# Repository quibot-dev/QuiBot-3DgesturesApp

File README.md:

# Qui-Bot H₂O
Documentació oficial i codi del Projecte QuiBot (UPC).

🌐 **Lloc web del projecte:** [https://quibot.upc.edu]

Robot humanoide educatiu que introdueix la programació seqüencial i la química
a infants de primària. Es mou per un tauler de joc amb línies negres, seguint
seqüències d'ordres, i manipula líquids de colors amb dues xeringues.

Admet tres vies de control:

- **Blocs de colors.** S'hi introdueixen cubs de fusta i el robot en llegeix el
  color i executa l'acció corresponent. És la via original del projecte.
- **Gestos.** Un sensor davant la cara reconeix sis ordres de moviment, amb
  confirmació abans d'executar-les.
- **Control remot per Wi-Fi.** El robot serveix una pàgina web que s'obre des
  del navegador de qualsevol telèfon o ordinador de la mateixa xarxa, sense
  instal·lar res.

## Contingut del repositori

| Directori | Contingut |
|---|---|
| `3D/` | Peces en STL, fitxers de disseny, model del conjunt en FreeCAD, captures amb l'orientació d'impressió i els paràmetres de cada perfil |
| `PCB/` | Projecte KiCad, fitxers de fabricació en Gerber, esquema elèctric i vista 3D |
| `src/` | Programa de control, servidor web i programes de verificació |
| `doc/` | Llista de material i memòria del treball |
| `User_manual/` | Guia d'ús del robot per a tallers i vídeo de demostració |

La **guia de muntatge**, de trenta-set passos, és l'annex A de la memòria.

## Maquinari

El control corre sobre una **Raspberry Pi Zero W** muntada sobre una placa
dissenyada per al projecte. Els motors pas a pas es governen amb controladors
A4988 i els polsos es generen per programari amb `pigpio`.

Els sensors són el TCS34725 per al color dels blocs, el PAJ7620U2 per als
gestos, el VL53L0X per a la distància als recipients i dos TCRT5000 per al
seguiment de línia, llegits a través d'un convertidor ADS1115. Els ulls són
dues matrius de LED WS2811.

## Posada en marxa

Cal Raspberry Pi OS Lite de 32 bits. El procediment complet és a l'annex D de
la memòria; en resum:

**1. Busos i pins.** Afegiu a `/boot/firmware/config.txt`:

```
dtparam=i2c_arm=on
dtoverlay=i2c-gpio,bus=3,i2c_gpio_sda=0,i2c_gpio_scl=1
gpio=4,5,6=op,dh
```

La tercera línia imposa nivell alt als pins d'habilitació dels controladors des
de l'arrencada i evita que els motors quedin energitzats i brunzint.

**2. Mòdul d'accés als busos:**

```bash
sudo modprobe i2c-dev
echo i2c-dev | sudo tee -a /etc/modules
```

Reinicieu. `ls /dev/i2c-*` ha de mostrar els dos busos.

**3. Entorn de Python:**

```bash
python3 -m venv ~/.venv
~/.venv/bin/pip install pigpio smbus2 flask rpi_ws281x \
    adafruit-circuitpython-ads1x15 \
    adafruit-circuitpython-tcs34725 \
    adafruit-circuitpython-vl53l0x \
    adafruit-extended-bus
```

**4. Dimoni de control dels pins:**

```bash
sudo systemctl enable --now pigpiod
```

**5. Execució:**

```bash
~/.venv/bin/python3 quibot.py
```

El programa escriu a la sortida l'adreça del control remot, que escolta al
port 8000. Per arrencar-lo automàticament amb la màquina, l'annex D descriu el
servei de systemd corresponent.

Els programes de `src/tests/` permeten comprovar els motors i cada sensor per
separat, cosa que convé fer amb la placa encara accessible.

## Procedència i llicències

L'estructura mecànica i el disseny original del robot provenen del projecte
[Qui-Bot H₂O de La Codornella](https://github.com/lacodornella/QuiBot), d'on
surten també les captures d'orientació d'impressió que es reprodueixen aquí.
Dues peces s'han redissenyat i la placa de control és obra de l'equip del
projecte. El control per gestos, el control remot i la documentació són feina
d'aquest treball.

| Element | Llicència |
|---|---|
| Maquinari: peces 3D, PCB i Gerbers | CERN-OHL-S v2 |
| Programari: codi de control | GPL v3 |
| Documentació: guia de muntatge, BOM i manual | CC BY-SA 4.0 |

Totes tres són recíproques: permeten usar, modificar i redistribuir el
material amb la condició que les obres derivades es publiquin en les mateixes
condicions.

> 📢 **Aviseu-nos si feu servir o adapteu aquest material!**  
> Si teniu pensat replicar el projecte, utilitzar aquest material en la vostra recerca o desenvolupar una versió derivada, us agrairem molt que ens ho feu saber enviant un correu a [quibot@upc.edu](mailto:quibot@upc.edu) o obrint una *Issue* en aquest repositori. Això ens ajuda a fer el seguiment de l'impacte del projecte.

---

## 👥 Autors, Equip i Agraïments

* **Investigadors Principals:** Marta Tarrés i Toni Dorado — Grup de Recerca RISS, Universitat Politècnica de Catalunya (UPC).
* **Desenvolupament i Integració (TFG/TFM):** Pau Anguera Comas 
* **Finançament:** Projecte finançat pel Departament d'Igualtat i Feminismes de la Generalitat de Catalunya (`IFE038/24/000087`).

* ## ⚠️ Avís Legal, Seguretat i Suport

* **Exempció de responsabilitat:** Aquest repositori i tots els seus materials es proporcionen "tal com són" (*AS IS*), amb fins exclusivament docents i de recerca. Els autors i la Universitat Politècnica de Catalunya (UPC) no assumeixen cap responsabilitat per danys directes, indirectes o derivats de la fabricació, muntatge, manipulació o ús dels dissenys, circuits o codis d'aquest projecte.
* **Seguretat mecatrònica:** El dispositiu conté components elèctrics i elements mecànics en moviment. Cal prendre les precaucions de seguretat adients durant la seva manipulació i alimentació elèctrica.
* **Atenció i suport tècnic:** Aquest projecte es manté exclusivament en el marc de les activitats de recerca del grup RISS. L'equip investigador no assumeix cap compromís d'oferir assistència tècnica, suport personalitzat o resolució de peticions a tercers usuaris.

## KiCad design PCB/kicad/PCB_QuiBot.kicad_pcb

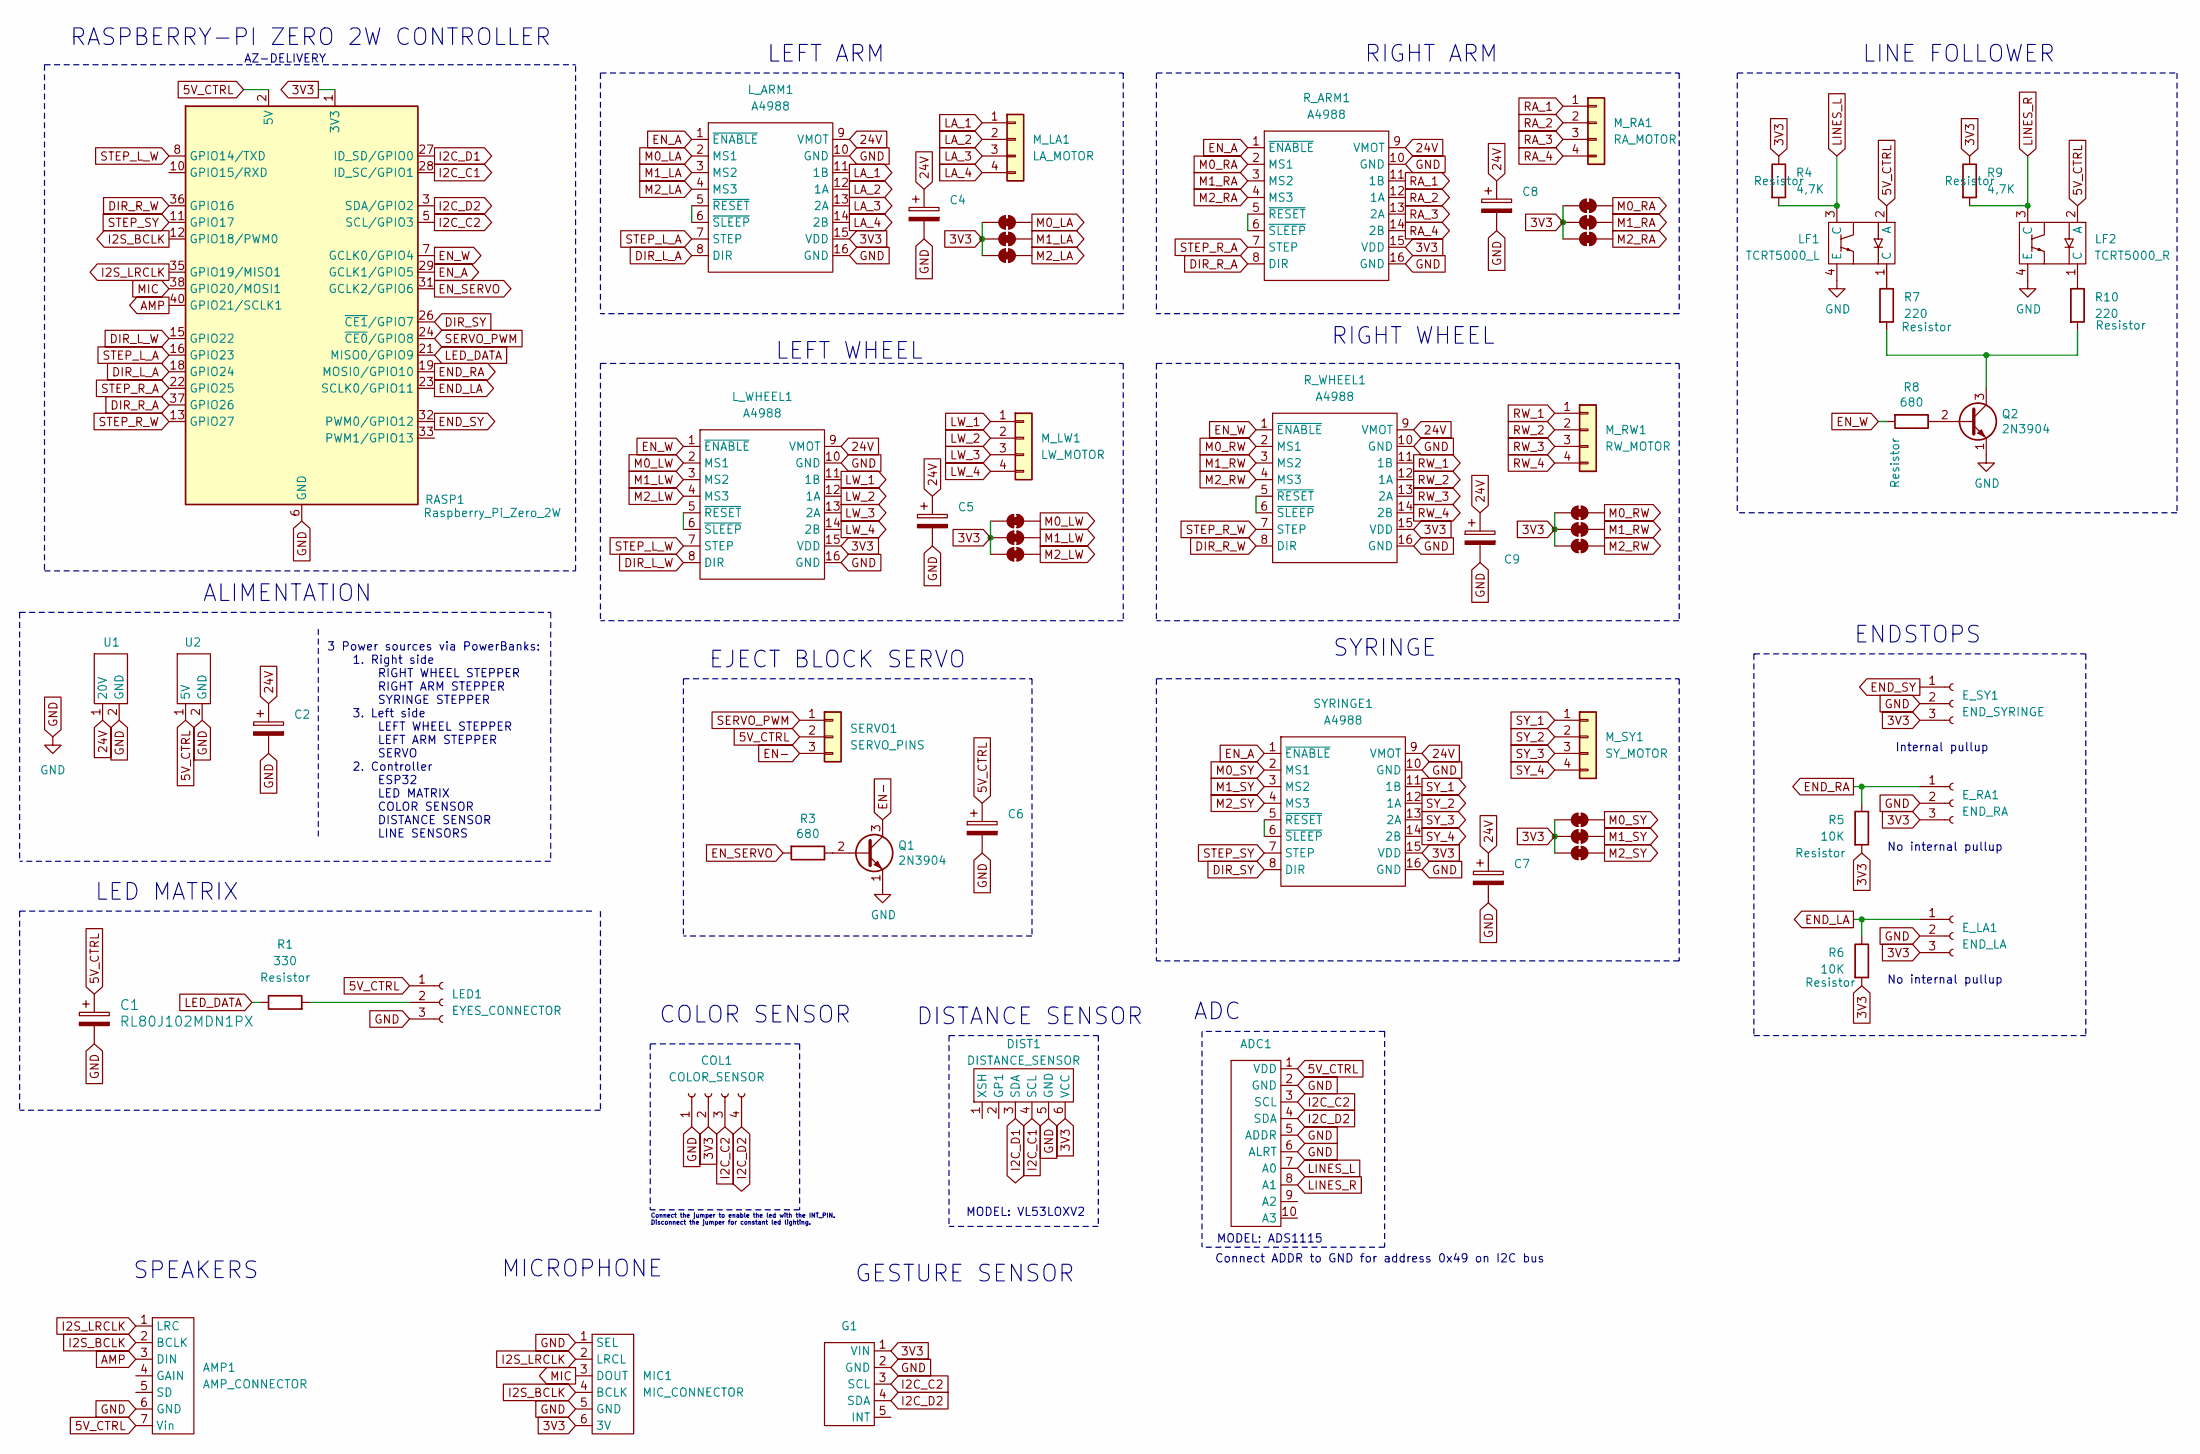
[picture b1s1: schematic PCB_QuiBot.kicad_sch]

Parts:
ADC1: PinHeader_1x10_P2.54mm_Vertical
AMP1: AMP_CONNECTOR; PinHeader_1x07_P2.54mm_Vertical
C1: RL80J102MDN1PX; CAP_RE5_8X8_NCH
C2: C_Polarized; CP_Radial_D10.0mm_P5.00mm
C4, C5, C6, C7, C8, C9: C_Polarized; CP_Radial_D6.3mm_P2.50mm
COL1: COLOR_SENSOR; PinHeader_1x04_P2.54mm_Vertical
DIST1: DISTANCE_SENSOR; PinHeader_1x06_P2.54mm_Vertical
E_LA1: END_LA; PinHeader_1x03_P2.54mm_Vertical
E_RA1: END_RA; PinHeader_1x03_P2.54mm_Vertical
E_SY1: END_SYRINGE; PinHeader_1x03_P2.54mm_Vertical
G1: PinHeader_1x05_P2.54mm_Vertical
LA0, LA1, LA2: SolderJumper_2_Bridged; SolderJumper-2_P1.3mm_Open_RoundedPad1.0x1.5mm
LED1: EYES_CONNECTOR; PinHeader_1x03_P2.54mm_Vertical
LF1: TCRT5000_L; TCRT5000_Line_follower
LF2: TCRT5000_R; TCRT5000_Line_follower
LW0, LW1, LW2: SolderJumper_2_Bridged; SolderJumper-2_P1.3mm_Open_RoundedPad1.0x1.5mm
L_ARM1: A4988; A4988_stepper_driver
L_WHEEL1: A4988; A4988_stepper_driver
MIC1: MIC_CONNECTOR; PinHeader_1x06_P2.54mm_Vertical
M_LA1: LA_MOTOR; PinHeader_1x04_P2.54mm_Vertical
M_LW1: LW_MOTOR; PinHeader_1x04_P2.54mm_Vertical
M_RA1: RA_MOTOR; PinHeader_1x04_P2.54mm_Vertical
M_RW1: RW_MOTOR; PinHeader_1x04_P2.54mm_Vertical
M_SY1: SY_MOTOR; PinHeader_1x04_P2.54mm_Vertical
Q1, Q2: 2N3904; TO-92_Inline
R1: 330; R_Axial_DIN0207_L6.3mm_D2.5mm_P10.16mm_Horizontal
R3, R8: 680; R_Axial_DIN0207_L6.3mm_D2.5mm_P10.16mm_Horizontal
R4, R9: 4,7K; R_Axial_DIN0207_L6.3mm_D2.5mm_P10.16mm_Horizontal
R5, R6: 10K; R_Axial_DIN0207_L6.3mm_D2.5mm_P10.16mm_Horizontal
R7, R10: 220; R_Axial_DIN0207_L6.3mm_D2.5mm_P10.16mm_Horizontal
RA0, RA1, RA2: SolderJumper_2_Bridged; SolderJumper-2_P1.3mm_Open_RoundedPad1.0x1.5mm
RASP1: Raspberry_Pi_Zero_2W; PinHeader_2x20_P2.54mm_Vertical
RW0, RW1, RW2: SolderJumper_2_Bridged; SolderJumper-2_P1.3mm_Open_RoundedPad1.0x1.5mm
R_ARM1: A4988; A4988_stepper_driver
R_WHEEL1: A4988; A4988_stepper_driver
SERVO1: SERVO_PINS; PinHeader_1x03_P2.54mm_Vertical
SY0, SY1, SY2: SolderJumper_2_Bridged; SolderJumper-2_P1.3mm_Open_RoundedPad1.0x1.5mm
SYRINGE1: A4988; A4988_stepper_driver
U1, U2: PowerConnector

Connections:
3V3: COL1.2, DIST1.6 (VCC), E_LA1.3, E_RA1.3, E_SY1.3, G1.1 (VIN), LA0.1 (A), LA1.1 (A), LA2.1 (A), LW0.1 (A), LW1.1 (A), LW2.1 (A), L_ARM1.15 (VDD), L_WHEEL1.15 (VDD), MIC1.6 (3V), R4.1, R5.2, R6.2, R9.1, RA0.1 (A), RA1.1 (A), RA2.1 (A), RASP1.1 (3V3), RASP1.17 (3V3), RW0.1 (A), RW1.1 (A), RW2.1 (A), R_ARM1.15 (VDD), R_WHEEL1.15 (VDD), SY0.1 (A), SY1.1 (A), SY2.1 (A), SYRINGE1.15 (VDD)
24V: C2.1, C4.1, C5.1, C7.1, C8.1, C9.1, L_ARM1.9 (VMOT), L_WHEEL1.9 (VMOT), R_ARM1.9 (VMOT), R_WHEEL1.9 (VMOT), SYRINGE1.9 (VMOT), U1.1 (20V)
AMP: AMP1.3 (DIN), RASP1.40 (GPIO21/SCLK1)
DIR_L_A: L_ARM1.8 (DIR), RASP1.18 (GPIO24)
DIR_L_W: L_WHEEL1.8 (DIR), RASP1.15 (GPIO22)
DIR_R_A: RASP1.37 (GPIO26), R_ARM1.8 (DIR)
DIR_R_W: RASP1.36 (GPIO16), R_WHEEL1.8 (DIR)
DIR_SY: RASP1.26 (~CE1/GPIO7), SYRINGE1.8 (DIR)
EN-: Q1.3 (C), SERVO1.3
END_LA: E_LA1.1, R6.1, RASP1.23 (SCLK0/GPIO11)
END_RA: E_RA1.1, R5.1, RASP1.19 (MOSI0/GPIO10)
END_SY: E_SY1.1, RASP1.32 (PWM0/GPIO12)
EN_A: L_ARM1.1 (~ENABLE), RASP1.29 (GCLK1/GPIO5), R_ARM1.1 (~ENABLE), SYRINGE1.1 (~ENABLE)
EN_SERVO: R3.2, RASP1.31 (GCLK2/GPIO6)
EN_W: L_WHEEL1.1 (~ENABLE), R8.2, RASP1.7 (GCLK0/GPIO4), R_WHEEL1.1 (~ENABLE)
GND: ADC1.2 (GND), ADC1.5 (ADDR), ADC1.6 (ALRT), AMP1.6 (GND), C1.2, C2.2, C4.2, C5.2, C6.2, C7.2, C8.2, C9.2, COL1.1, DIST1.5 (GND), E_LA1.2, E_RA1.2, E_SY1.2, G1.2 (GND), LED1.3, LF1.4 (E), LF2.4 (E), L_ARM1.10 (GND), L_ARM1.16 (GND), L_WHEEL1.10 (GND), L_WHEEL1.16 (GND), MIC1.1 (SEL), MIC1.5 (GND), Q1.1 (E), Q2.1 (E), RASP1.6 (GND), RASP1.9 (GND), RASP1.14 (GND), RASP1.20 (GND), RASP1.25 (GND), RASP1.30 (GND), RASP1.34 (GND), RASP1.39 (GND), R_ARM1.10 (GND), R_ARM1.16 (GND), R_WHEEL1.10 (GND), R_WHEEL1.16 (GND), SYRINGE1.10 (GND), SYRINGE1.16 (GND), U1.2 (GND), U2.2 (GND)
I2C_C1: DIST1.4 (SCL), RASP1.28 (ID_SC/GPIO1)
I2C_C2: ADC1.3 (SCL), COL1.3, G1.3 (SCL), RASP1.5 (SCL/GPIO3)
I2C_D1: DIST1.3 (SDA), RASP1.27 (ID_SD/GPIO0)
I2C_D2: ADC1.4 (SDA), COL1.4, G1.4 (SDA), RASP1.3 (SDA/GPIO2)
I2S_BCLK: AMP1.2 (BCLK), MIC1.4 (BCLK), RASP1.12 (GPIO18/PWM0)
I2S_LRCLK: AMP1.1 (LRC), MIC1.2 (LRCL), RASP1.35 (GPIO19/MISO1)
LA_1: L_ARM1.11 (1B), M_LA1.1
LA_2: L_ARM1.12 (1A), M_LA1.2
LA_3: L_ARM1.13 (2A), M_LA1.3
LA_4: L_ARM1.14 (2B), M_LA1.4
LED_DATA: R1.1, RASP1.21 (MISO0/GPIO9)
LINES_L: ADC1.7 (A0), LF1.3 (C), R4.2
LINES_R: ADC1.8 (A1), LF2.3 (C), R9.2
LW_1: L_WHEEL1.11 (1B), M_LW1.1
LW_2: L_WHEEL1.12 (1A), M_LW1.2
LW_3: L_WHEEL1.13 (2A), M_LW1.3
LW_4: L_WHEEL1.14 (2B), M_LW1.4
M0_LA: LA0.2 (B), L_ARM1.2 (MS1)
M0_LW: LW0.2 (B), L_WHEEL1.2 (MS1)
M0_RA: RA0.2 (B), R_ARM1.2 (MS1)
M0_RW: RW0.2 (B), R_WHEEL1.2 (MS1)
M0_SY: SY0.2 (B), SYRINGE1.2 (MS1)
M1_LA: LA1.2 (B), L_ARM1.3 (MS2)
M1_LW: LW1.2 (B), L_WHEEL1.3 (MS2)
M1_RA: RA1.2 (B), R_ARM1.3 (MS2)
M1_RW: RW1.2 (B), R_WHEEL1.3 (MS2)
M1_SY: SY1.2 (B), SYRINGE1.3 (MS2)
M2_LA: LA2.2 (B), L_ARM1.4 (MS3)
M2_LW: LW2.2 (B), L_WHEEL1.4 (MS3)
M2_RA: RA2.2 (B), R_ARM1.4 (MS3)
M2_RW: RW2.2 (B), R_WHEEL1.4 (MS3)
M2_SY: SY2.2 (B), SYRINGE1.4 (MS3)
MIC: MIC1.3 (DOUT), RASP1.38 (GPIO20/MOSI1)
unnamed: LED1.2, R1.2
unnamed: LF1.1 (C), R7.1
unnamed: LF2.1 (C), R10.1
unnamed: L_ARM1.5 (~RESET), L_ARM1.6 (~SLEEP)
unnamed: L_WHEEL1.5 (~RESET), L_WHEEL1.6 (~SLEEP)
unnamed: Q1.2 (B), R3.1
unnamed: Q2.2 (B), R8.1
unnamed: Q2.3 (C), R7.2, R10.2
unnamed: R_ARM1.5 (~RESET), R_ARM1.6 (~SLEEP)
unnamed: R_WHEEL1.5 (~RESET), R_WHEEL1.6 (~SLEEP)
unnamed: SYRINGE1.5 (~RESET), SYRINGE1.6 (~SLEEP)
RA_1: M_RA1.1, R_ARM1.11 (1B)
RA_2: M_RA1.2, R_ARM1.12 (1A)
RA_3: M_RA1.3, R_ARM1.13 (2A)
RA_4: M_RA1.4, R_ARM1.14 (2B)
RW_1: M_RW1.1, R_WHEEL1.11 (1B)
RW_2: M_RW1.2, R_WHEEL1.12 (1A)
RW_3: M_RW1.3, R_WHEEL1.13 (2A)
RW_4: M_RW1.4, R_WHEEL1.14 (2B)
SERVO_PWM: RASP1.24 (~CE0/GPIO8), SERVO1.1
STEP_L_A: L_ARM1.7 (STEP), RASP1.16 (GPIO23)
STEP_L_W: L_WHEEL1.7 (STEP), RASP1.8 (GPIO14/TXD)
STEP_R_A: RASP1.22 (GPIO25), R_ARM1.7 (STEP)
STEP_R_W: RASP1.13 (GPIO27), R_WHEEL1.7 (STEP)
STEP_SY: RASP1.11 (GPIO17), SYRINGE1.7 (STEP)
SY_1: M_SY1.1, SYRINGE1.11 (1B)
SY_2: M_SY1.2, SYRINGE1.12 (1A)
SY_3: M_SY1.3, SYRINGE1.13 (2A)
SY_4: M_SY1.4, SYRINGE1.14 (2B)

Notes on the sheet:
No internal pullup
ADC
ALIMENTATION
SPEAKERS
MODEL: VL53LOXV2
RIGHT WHEEL
COLOR SENSOR
EJECT BLOCK SERVO
ENDSTOPS
LEFT ARM
RASPBERRY-PI ZERO 2W CONTROLLER
Connect ADDR to GND for address 0x49 on I2C bus
MODEL: ADS1115
GESTURE SENSOR
AZ-DELIVERY
SYRINGE
LINE FOLLOWER
MICROPHONE
LEFT WHEEL
DISTANCE SENSOR
LED MATRIX
3 Power sources via PowerBanks: 1. Right side RIGHT WHEEL STEPPER RIGHT ARM STEPPER SYRINGE STEPPER 3. Left side LEFT WHEEL STEPPER LEFT ARM STEPPER SERVO 2. Controller ESP32 LED MATRIX COLOR SENSOR DISTANCE SENSOR LINE SENSORS
Internal pullup
Connect the jumper to enable the led with the INT_PIN. Disconnect the jumper for constant led lighting.
RIGHT ARM

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
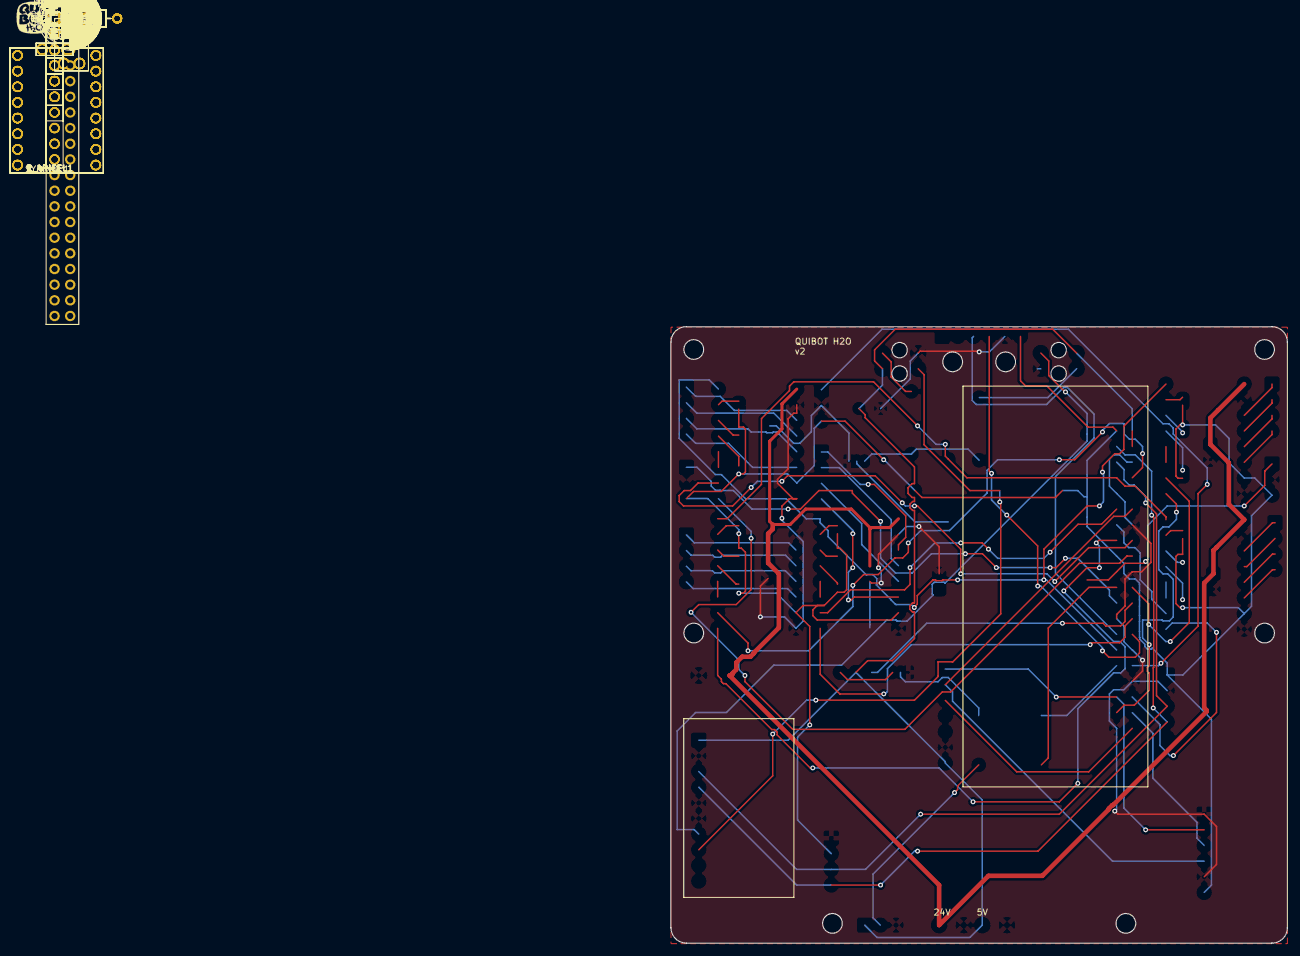
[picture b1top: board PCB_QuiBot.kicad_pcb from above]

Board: 2 copper layers, 100.0 x 100.0 mm, 60 parts (0 on the bottom side), 79 nets.

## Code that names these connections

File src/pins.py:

# Copyright (C) 2026 Pau Anguera Comas
#
# Aquest programa és programari lliure: podeu redistribuir-lo i/o
# modificar-lo sota els termes de la Llicència Pública General de GNU
# publicada per la Free Software Foundation, en la versió 3.
#
# Es distribueix amb l'esperança que sigui útil, però SENSE CAP GARANTIA.
# Vegeu la Llicència Pública General de GNU per a més detalls.
# <https://www.gnu.org/licenses/>

"""
pins.py — Definició de pins GPIO (BCM) de la Raspberry Pi Zero 2W.

Valors extrets del connector RASP1 del projecte KiCad de la placa
(projecte-quibot-master), verificats pin a pin contra l'esquemàtic.

Tots els números fan referència a la numeració BCM.
"""

# ==================
# MOTORS (drivers A4988)
# ==================

# Enables (actius a LOW), compartits per parelles
EN_W     = 4    # enable rodes
EN_A     = 5    # enable braços
EN_SERVO = 6    # enable subsistema servo + xeringa

# Servo d'expulsió de blocs
SERVO_PWM = 8   # GPIO8 (CE0)

# Motor pas a pas xeringa
STEP_SY = 17
DIR_SY  = 7

# Motor pas a pas roda dreta
STEP_R_W = 27
DIR_R_W  = 16

# Motor pas a pas roda esquerra
STEP_L_W = 14
DIR_L_W  = 22

# Motor pas a pas braç dret
STEP_R_A = 25
DIR_R_A  = 26

# Motor pas a pas braç esquerre
STEP_L_A = 23
DIR_L_A  = 24

# ==================
# SENSORS — busos I2C
# ==================

# Bus I2C del sensor de color TCS34725 (GPIO2/3, hardware i2c-1).
# En aquest MATEIX bus hi pengen també el PAJ7620U2 (gestos) i l'ADS1115 (línia).
SDA_COL = 2
SCL_COL = 3

# Sensor de gestos PAJ7620U2 — MATEIX bus que el color (GPIO2/3)
SDA_GEST = SDA_COL
SCL_GEST = SCL_COL
# INT del PAJ7620U2 NO connectat a la PCB -> el driver usa polling

# Bus I2C del sensor de distància VL53L0X (GPIO0/1, software i2c-gpio), sol al bus
SDA_DIST = 0
SCL_DIST = 1

# Finals de carrera (efecte Hall)
END_RA = 10   # braç dret     (pullup extern 10k a la PCB)
END_LA = 11   # braç esquerre (pullup extern 10k a la PCB)
END_SY = 12   # xeringa       (SENSE pullup extern -> cal PUD_UP per software)

# Sensors seguidors de línia (TCRT5000) -> canals de l'ADS1115, NO són GPIO
LINES_L = 0   # canal AIN0 de l'ADS1115
LINES_R = 1   # canal AIN1 de l'ADS1115

# ==================
# DISPLAY
# ==================

# Dades matriu LED 8x8 RGB WS2811 (2x ull)
# Originalment a GPIO9 (a la PCB), però GPIO9 NO té PWM/PCM/SPI per hardware i
# pigpio (1µs) no pot fer el timing WS2811 (el bit "0" surt com "1" -> tot blanc).
# Solucio: pont fisic GPIO13 -> GPIO9 (GPIO13 = PWM1, valid per a rpi_ws281x) i
# LED_DATA passa a 13. IMPORTANT: GPIO9 s'ha de deixar com a ENTRADA (alta
# impedancia) perque no lluiti amb GPIO13 (ho fa eyes_setup / LED_DATA_OLD).
LED_DATA     = 13   # nou pin de dades (PWM1), via pont a la PCB
LED_DATA_OLD = 9    # pin antic; cal deixar-lo en INPUT per no fer conflicte

# ==================
# ÀUDIO (afegit per company, no part d'aquest TFG)
# ==================

# I2S — amplificador + micròfon
I2C_BCLK  = 18
I2C_LRCLK = 19
MIC       = 20
AMP_DIN   = 21
